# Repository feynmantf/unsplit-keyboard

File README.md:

# this project has been archived and abandoned in pursuit of hall-effect
# ~~WIP!! (firmware and schematic work but i havent gotten around to the new pcb layout) - I will get back to working on it when the semester ends/when I have the time~~
## all files in [early revisions/final but with microcontrollers](/early%20revisions/final%20but%20with%20microcontrollers) still work and can be manufactured (see [BOM](/early%20revisions/final%20but%20with%20microcontrollers/bom%20and%20cpl%20files) and [Gerber](/early%20revisions/final%20but%20with%20microcontrollers/gerber%20and%20drill%20files) folders), i just dont like the layout lol
## i plan on coming back to this project sometime before the end of 2024, but i cant promise it will look the same

# kaluza kb
kaluza kb pcb, layout, and case files (plus other useful stuff like firmware/images)
(documentation in progress)

## design logic
i wanted a keyboard that was both 65% and had extra function keys. i also wanted an oled panel and rotary encoder. and, as an added bonus, i love seeing through hole components on a keyboard. therefore, all of these features have been included

## sample images (they exist for the old revisions if you want to dig through the file tree)

### case images/renders:

### pcb images/renders:
#### pcb front (old version):

#### pcb back (old version):

### schematic (new version):

### handwired circuit test images:
.JPG)
.JPG)

## parts needed to build the board (not included in these files)
### parts you must source
- keyswitches (x80)
- keycaps (base kit and spacebar)
- pcb stabilizers (2u x4 and 6.25u x1)
- rotary knob (x1)
- rotary encoder (ec11 with switch) (x1)
- oled (0.91 inch, SSD1306) (x1)
- switch diodes (x80)
- elite-c v4 (x1)

### parts to get manufactured
- pcb
- plate (carbon fiber or sheet metal) (2mm)
- case (3d printed)
- leaf springs (carbon fiber) (1mm)

## basic instructions
- buy all the parts listed above
- get the pcb printed (from jlcpcb or some other service)
- get the plate, case, and leaf springs printed
- flash firmware and test the board to make sure everything works
- screw stabilizers into pcb
- align and place plate on top of pcb
- clip switches into place and slot them into the pcb
- solder switches to the pcb (locations marked on pcb)
- solder rotary encoder onto pcb (locations marked on pcb)
- solder oled panel onto pcb (locations marked on pcb)
- test everything again
- screw leaf springs into pcb (locations marked on pcb)
- put assembled pcb and plate in the case, and screw the case together
- you should be done now !!

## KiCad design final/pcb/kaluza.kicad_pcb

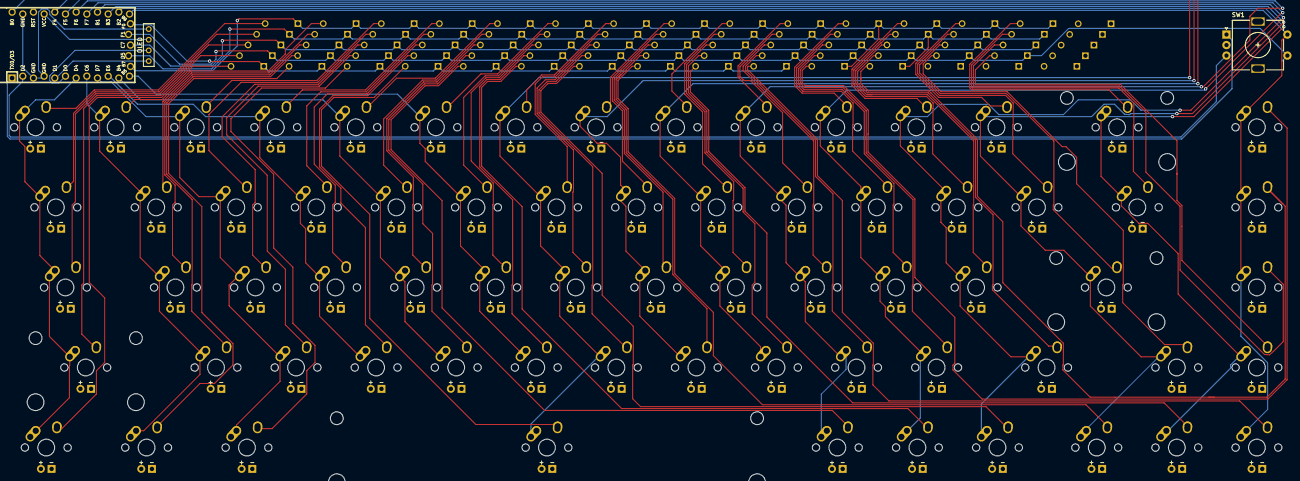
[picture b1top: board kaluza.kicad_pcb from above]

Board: 2 copper layers, 146 parts (0 on the bottom side), 94 nets.

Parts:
D1, D2, D3, D4, D5, D6, D7, D8, D9, D10, D11, D12, D13, D14, D15, D16, D17, D18, D19, D20, D21, D22, D23, D24, D25, D26, D27, D28, D29, D30, D31, D32, D33, D34, D35, D36, D37, D38, D39, D40, D41, D42, D43, D44, D45, D46, D47, D48, D49, D50, D51, D52, D53, D54, D55, D56, D57, D58, D59, D60, D61, D62, D63, D64, D65, D66, D67, D68: SMD_123; Diode-Hybrid-Back
D_Spare: SMD_123; Diode-Hybrid-Back
D_Spare#2, D_Spare#3, D_Spare#4, D_Spare#5, D_Spare#6, D_Spare#7: SMD_123; Diode-Hybrid-Back
MX1, MX2, MX3, MX4, MX5, MX6, MX7, MX8, MX9, MX10, MX11, MX12, MX13, MX15, MX17, MX18, MX19, MX20, MX21, MX22, MX23, MX24, MX25, MX26, MX27, MX28, MX30, MX32, MX33, MX34, MX35, MX36, MX37, MX38, MX39, MX40, MX41, MX42, MX44, MX46, MX47, MX48, MX49, MX50, MX51, MX52, MX53, MX54, MX55, MX57, MX58, MX63, MX64, MX65, MX66, MX67, MX68: MX-NoLED-MX_Alps_Hybrid; MX-1U
MX14: MX-NoLED-MX_Alps_Hybrid; MX-2U
MX16, MX29: MX-NoLED-MX_Alps_Hybrid; MX-1.5U
MX31, MX56: MX-NoLED-MX_Alps_Hybrid; MX-1.75U
MX43, MX45: MX-NoLED-MX_Alps_Hybrid; MX-2.25U
MX59, MX60, MX61: MX-NoLED-MX_Alps_Hybrid; MX-1.25U
MX62: MX-NoLED-MX_Alps_Hybrid; MX-6.25U
OL1: OLED-kbd; OLED
SW1: Rotary_Encoder_Switch; RotaryEncoder_Alps_EC11E-Switch_Vertical_H20mm
U1: Elite-C; Elite-C-ZigZag

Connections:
COL_0: MX1.1, MX16.1, MX31.1, MX45.1, MX59.1, U1.7
COL_1: MX2.1, MX17.1, MX32.1, MX46.1, MX60.1, U1.8
COL_2: MX3.1, MX18.1, MX33.1, MX47.1, MX61.1, U1.9
COL_3: MX4.1, MX19.1, MX34.1, MX48.1, U1.10
COL_4: MX5.1, MX20.1, MX35.1, MX49.1, U1.11
COL_5: MX6.1, MX21.1, MX36.1, MX50.1, U1.12
COL_6: MX7.1, MX22.1, MX37.1, MX51.1, MX62.1, U1.24
COL_7: MX8.1, MX23.1, MX38.1, MX52.1, U1.20
COL_8: MX9.1, MX24.1, MX39.1, MX53.1, U1.19
COL_9: MX10.1, MX25.1, MX40.1, MX54.1, MX63.1, U1.18
COL_10: MX11.1, MX26.1, MX41.1, MX55.1, MX64.1, U1.17
COL_11: MX12.1, MX27.1, MX42.1, MX56.1, MX65.1, U1.16
COL_12: MX13.1, MX28.1, MX43.1, MX57.1, MX66.1, U1.15
COL_13: MX14.1, MX29.1, MX58.1, MX67.1, U1.14
COL_14: MX15.1, MX30.1, MX44.1, MX68.1, SW1.S2, U1.13
GND: OL1.4, SW1.C, U1.3, U1.4, U1.23
unnamed: D1.2, MX1.2
unnamed: D2.2, MX2.2
unnamed: D3.2, MX3.2
unnamed: D4.2, MX4.2
unnamed: D5.2, MX5.2
unnamed: D6.2, MX6.2
unnamed: D7.2, MX7.2
unnamed: D8.2, MX8.2
unnamed: D9.2, MX9.2
unnamed: D10.2, MX10.2
unnamed: D11.2, MX11.2
unnamed: D12.2, MX12.2
unnamed: D13.2, MX13.2
unnamed: D14.2, MX14.2
unnamed: D15.2, MX15.2
unnamed: D16.2, MX16.2
unnamed: D17.2, MX17.2
unnamed: D18.2, MX18.2
unnamed: D19.2, MX19.2
unnamed: D20.2, MX20.2
unnamed: D21.2, MX21.2
unnamed: D22.2, MX22.2
unnamed: D23.2, MX23.2
unnamed: D24.2, MX24.2
unnamed: D25.2, MX25.2
unnamed: D26.2, MX26.2
unnamed: D27.2, MX27.2
unnamed: D28.2, MX28.2
unnamed: D29.2, MX29.2
unnamed: D30.2, MX30.2
unnamed: D31.2, MX31.2
unnamed: D32.2, MX32.2
unnamed: D33.2, MX33.2
unnamed: D34.2, MX34.2
unnamed: D35.2, MX35.2
unnamed: D36.2, MX36.2
unnamed: D37.2, MX37.2
unnamed: D38.2, MX38.2
unnamed: D39.2, MX39.2
unnamed: D40.2, MX40.2
unnamed: D41.2, MX41.2
unnamed: D42.2, MX42.2
unnamed: D43.2, MX43.2
unnamed: D44.2, MX44.2
unnamed: D45.2, MX45.2
unnamed: D46.2, MX46.2
unnamed: D47.2, MX47.2
unnamed: D48.2, MX48.2
unnamed: D49.2, MX49.2
unnamed: D50.2, MX50.2
unnamed: D51.2, MX51.2
unnamed: D52.2, MX52.2
unnamed: D53.2, MX53.2
unnamed: D54.2, MX54.2
unnamed: D55.2, MX55.2
unnamed: D56.2, MX56.2
unnamed: D57.2, MX57.2
unnamed: D58.2, MX58.2
unnamed: D59.2, MX59.2
unnamed: D60.2, MX60.2
unnamed: D61.2, MX61.2
unnamed: D62.2, MX62.2
unnamed: D63.2, MX63.2
unnamed: D64.2, MX64.2
unnamed: D65.2, MX65.2
unnamed: D66.2, MX66.2
unnamed: D67.2, MX67.2
unnamed: D68.2, MX68.2
ROT_A: SW1.A, U1.1
ROT_B: SW1.B, U1.2
ROW0: D1.1, D2.1, D3.1, D4.1, D5.1, D6.1, D7.1, D8.1, D9.1, D10.1, D11.1, D12.1, D13.1, D14.1, D15.1, U1.25
ROW1: D16.1, D17.1, D18.1, D19.1, D20.1, D21.1, D22.1, D23.1, D24.1, D25.1, D26.1, D27.1, D28.1, D29.1, D30.1, U1.26
ROW2: D31.1, D32.1, D33.1, D34.1, D35.1, D36.1, D37.1, D38.1, D39.1, D40.1, D41.1, D42.1, D43.1, D44.1, U1.27
ROW3: D45.1, D46.1, D47.1, D48.1, D49.1, D50.1, D51.1, D52.1, D53.1, D54.1, D55.1, D56.1, D57.1, D58.1, SW1.S1, U1.28
ROW4: D59.1, D60.1, D61.1, D62.1, D63.1, D64.1, D65.1, D66.1, D67.1, D68.1, U1.29
SCL: OL1.2, U1.6
SDA: OL1.1, U1.5
VCC: OL1.3, U1.21

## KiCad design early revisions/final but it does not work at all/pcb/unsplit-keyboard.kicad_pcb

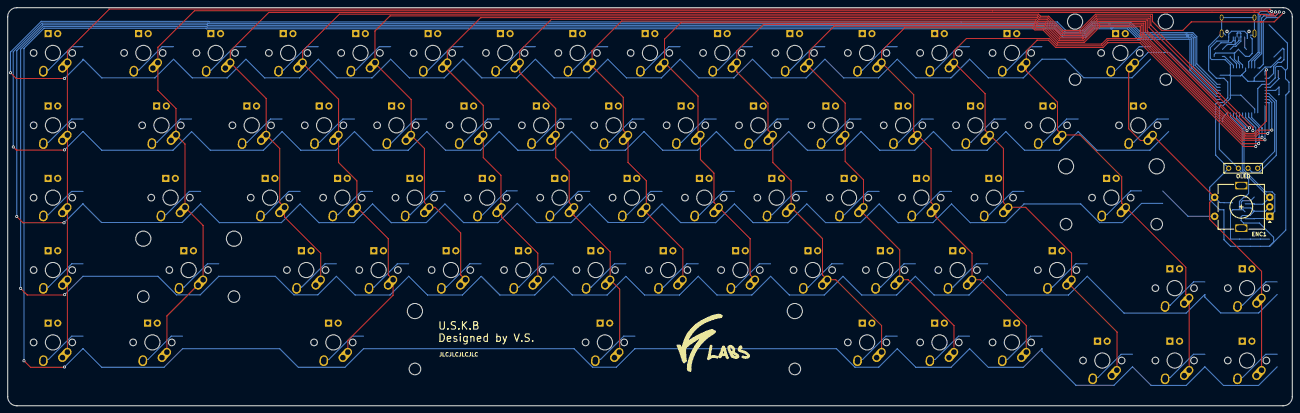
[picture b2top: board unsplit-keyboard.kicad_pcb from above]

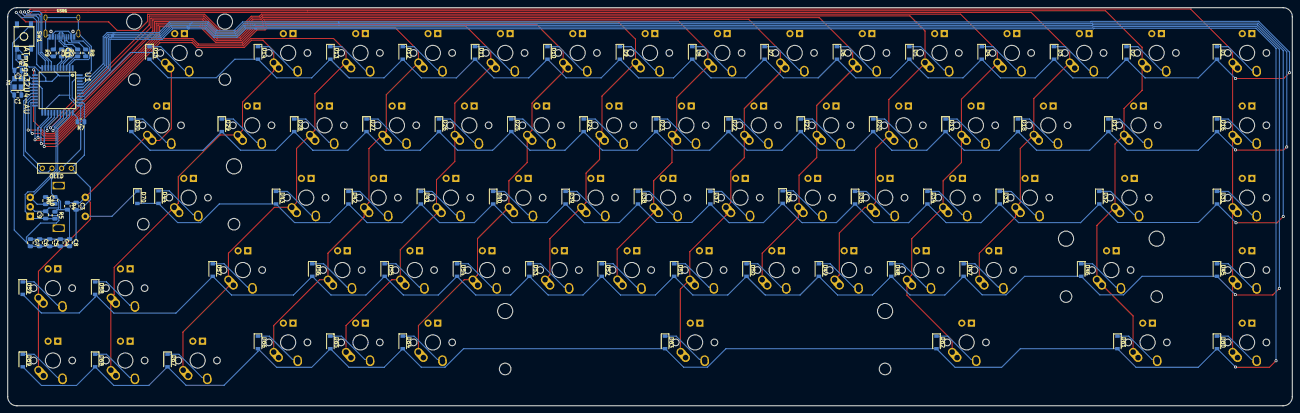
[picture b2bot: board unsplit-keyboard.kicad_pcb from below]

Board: 2 copper layers, 338.1 x 104.8 mm, 167 parts (94 on the bottom side), 107 nets.

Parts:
C1, C2: 22p; C_0805_2012Metric
C3, C4, C5, C6, C7, C9, C10: 0.1u; C_0805_2012Metric
C8: 4.7u; C_0805_2012Metric
C11: 1u; C_0805_2012Metric
D1, D2, D3, D4, D5, D6, D7, D8, D9, D10, D11, D12, D13, D14, D15, D16, D17, D18, D19, D20, D21, D22, D23, D24, D25, D26, D27, D28, D29, D30, D31, D32, D33, D34, D35, D36, D37, D38, D39, D40, D41, D42, D43, D44, D45, D46, D47, D48, D49, D50, D51, D52, D53, D54, D55, D56, D57, D58, D59, D60, D61, D62, D63, D64, D65, D66, D67, D68, D69, D70: D; D_SOD-123
ENC1: Rotary_Encoder_Switch; RotaryEncoder_Alps_EC11E-Switch_Vertical_H20mm
LOGO1: LOGO; logo
LOGO2: LOGO; labs
MX1, MX2, MX3, MX4, MX5, MX6, MX7, MX8, MX9, MX10, MX11, MX12, MX13, MX14, MX16, MX18, MX19, MX20, MX21, MX22, MX23, MX24, MX25, MX26, MX27, MX28, MX29, MX31, MX33, MX34, MX35, MX36, MX37, MX38, MX39, MX40, MX41, MX42, MX43, MX45, MX47, MX48, MX49, MX50, MX51, MX52, MX53, MX54, MX55, MX56, MX58, MX59, MX60, MX64, MX65, MX66, MX67, MX68, MX69: MX-NoLED-MX_Alps_Hybrid; MX-1U
MX15: MX-NoLED-MX_Alps_Hybrid; MX-2U
MX17, MX30: MX-NoLED-MX_Alps_Hybrid; MX-1.5U
MX32, MX57: MX-NoLED-MX_Alps_Hybrid; MX-1.75U
MX44, MX46: MX-NoLED-MX_Alps_Hybrid; MX-2.25U
MX61, MX62: MX-NoLED-MX_Alps_Hybrid; MX-1.25U
MX63: MX-NoLED-MX_Alps_Hybrid; MX-6.25U
OL1: OLED-kbd; OLED
R1, R4, R5, R6, R7: 10k; R_0805_2012Metric
R2, R3: 22; R_0805_2012Metric
R8, R9: 5.1k; R_0805_2012Metric
SW1: SW_PUSH; SKQG-1155865
U1: ATmega32U4-AU; ATMEGA32U4-AU
USB1: HRO-TYPE-C-31-M-12; HRO-TYPE-C-31-M-12-Assembly
X1: XTAL_GND; Crystal_SMD_3225-4pin_3.2x2.5mm

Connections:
COL0: MX1.1, MX16.1, MX31.1, MX45.1, MX60.1, U1.8
COL1: MX2.1, MX17.1, MX32.1, MX46.1, MX61.1, U1.9
COL2: MX3.1, MX18.1, MX33.1, MX47.1, U1.10
COL3: MX4.1, MX19.1, MX34.1, MX48.1, MX62.1, U1.11
COL4: MX5.1, MX20.1, MX35.1, MX49.1, U1.28
COL5: MX6.1, MX21.1, MX36.1, MX50.1, U1.29
COL6: MX7.1, MX22.1, MX37.1, MX51.1, MX63.1, U1.30
COL7: MX8.1, MX23.1, MX38.1, MX52.1, U1.12
COL8: MX9.1, MX24.1, MX39.1, MX53.1, U1.20
COL9: MX10.1, MX25.1, MX40.1, MX54.1, MX64.1, U1.21
COL10: MX11.1, MX26.1, MX41.1, MX55.1, MX65.1, U1.25
COL11: MX12.1, MX27.1, MX42.1, MX56.1, MX66.1, U1.22
COL12: MX13.1, MX28.1, MX43.1, MX57.1, MX67.1, U1.26
COL13: MX14.1, MX29.1, MX44.1, MX58.1, MX68.1, U1.27
COL14: C3.1, ENC1.S1, MX15.1, MX30.1, MX59.1, MX69.1, R4.1, U1.36
D+: R3.1, U1.4
D-: R2.1, U1.3
GND: C1.2, C2.2, C3.2, C4.2, C5.2, C6.2, C7.2, C8.2, C9.2, C10.1, C11.1, ENC1.C, OL1.4, R7.1, R8.2, R9.1, SW1.1, U1.5, U1.15, U1.23, U1.35, U1.43, USB1.1, USB1.12, USB1.13, X1.3
unnamed: C11.2, U1.6
unnamed: D1.1, MX1.2
unnamed: D2.1, MX2.2
unnamed: D3.1, MX3.2
unnamed: D4.1, MX4.2
unnamed: D5.1, MX5.2
unnamed: D6.1, MX6.2
unnamed: D7.1, MX7.2
unnamed: D8.1, MX8.2
unnamed: D9.1, MX9.2
unnamed: D10.1, MX10.2
unnamed: D11.1, MX11.2
unnamed: D12.1, MX12.2
unnamed: D13.1, MX13.2
unnamed: D14.1, MX14.2
unnamed: D15.1, MX15.2
unnamed: D16.1, MX16.2
unnamed: D17.1, MX17.2
unnamed: D18.1, MX18.2
unnamed: D19.1, MX19.2
unnamed: D20.1, MX20.2
unnamed: D21.1, MX21.2
unnamed: D22.1, MX22.2
unnamed: D23.1, MX23.2
unnamed: D24.1, MX24.2
unnamed: D25.1, MX25.2
unnamed: D26.1, MX26.2
unnamed: D27.1, MX27.2
unnamed: D28.1, MX28.2
unnamed: D29.1, MX29.2
unnamed: D30.1, MX30.2
unnamed: D31.1, MX31.2
unnamed: D32.1, MX32.2
unnamed: D33.1, MX33.2
unnamed: D34.1, MX34.2
unnamed: D35.1, MX35.2
unnamed: D36.1, MX36.2
unnamed: D37.1, MX37.2
unnamed: D38.1, MX38.2
unnamed: D39.1, MX39.2
unnamed: D40.1, MX40.2
unnamed: D41.1, MX41.2
unnamed: D42.1, MX42.2
unnamed: D43.1, MX43.2
unnamed: D44.1, MX44.2
unnamed: D45.1, MX45.2
unnamed: D46.1, MX46.2
unnamed: D47.1, MX47.2
unnamed: D48.1, MX48.2
unnamed: D49.1, MX49.2
unnamed: D50.1, MX50.2
unnamed: D51.1, MX51.2
unnamed: D52.1, MX52.2
unnamed: D53.1, MX53.2
unnamed: D54.1, MX54.2
unnamed: D55.1, MX55.2
unnamed: D56.1, MX56.2
unnamed: D57.1, MX57.2
unnamed: D58.1, MX58.2
unnamed: D59.1, MX59.2
unnamed: D60.1, MX60.2
unnamed: D61.1, MX61.2
unnamed: D62.1, MX62.2
unnamed: D63.1, MX63.2
unnamed: D64.1, MX64.2
unnamed: D65.1, MX65.2
unnamed: D66.1, MX66.2
unnamed: D67.1, MX67.2
unnamed: D68.1, MX68.2
unnamed: D69.1, MX69.2
unnamed: R2.2, USB1.5, USB1.7
unnamed: R3.2, USB1.6, USB1.8
unnamed: R7.2, U1.33
unnamed: R8.1, USB1.4
unnamed: R9.2, USB1.10
RESET: R1.1, SW1.2, U1.13
ROT_A: C9.1, ENC1.A, R5.2, U1.31
ROT_B: C10.2, ENC1.B, R6.1, U1.32
ROW0: D1.2, D2.2, D3.2, D4.2, D5.2, D6.2, D7.2, D8.2, D9.2, D10.2, D11.2, D12.2, D13.2, D14.2, D15.2, U1.41
ROW1: D16.2, D17.2, D18.2, D19.2, D20.2, D21.2, D22.2, D23.2, D24.2, D25.2, D26.2, D27.2, D28.2, D29.2, D30.2, U1.40
ROW2: D31.2, D32.2, D33.2, D34.2, D35.2, D36.2, D37.2, D38.2, D39.2, D40.2, D41.2, D42.2, D43.2, D44.2, D70.2, U1.39
ROW3: D45.2, D46.2, D47.2, D48.2, D49.2, D50.2, D51.2, D52.2, D53.2, D54.2, D55.2, D56.2, D57.2, D58.2, D59.2, U1.38
ROW4: D60.2, D61.2, D62.2, D63.2, D64.2, D65.2, D66.2, D67.2, D68.2, D69.2, U1.37
R_ENC: D70.1, ENC1.S2
SCL: OL1.2, U1.18
SDA: OL1.1, U1.19
VCC: C4.1, C5.1, C6.1, C7.1, C8.1, OL1.3, R1.2, R4.2, R5.1, R6.2, U1.2, U1.7, U1.14, U1.24, U1.34, U1.44, USB1.2, USB1.11
XTAL1: C1.1, U1.17, X1.1
XTAL2: C2.1, U1.16, X1.2

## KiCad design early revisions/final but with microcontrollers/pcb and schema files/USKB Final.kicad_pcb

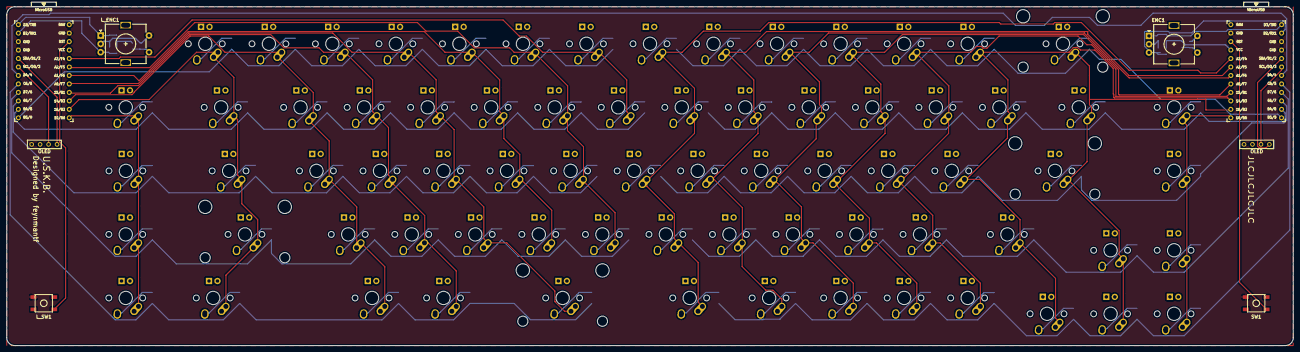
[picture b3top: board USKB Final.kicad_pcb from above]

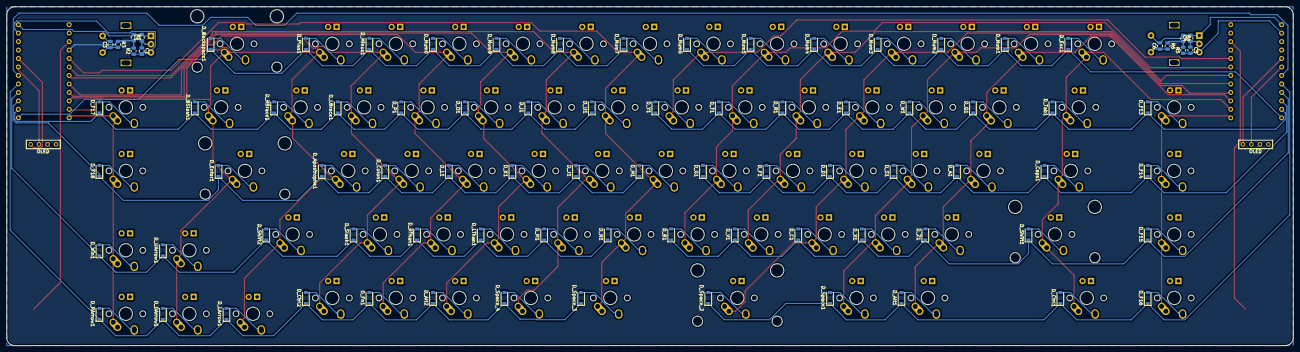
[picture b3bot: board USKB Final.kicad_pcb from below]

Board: 2 copper layers, 385.8 x 101.6 mm, 166 parts (85 on the bottom side), 114 nets.

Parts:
C1, C2, C3, C4, C5, C6: 0.1u; C_0805_2012Metric
D_A1: SMD_123; D_SOD-123
D_Alt1, D_Alt2: SMD_123; D_SOD-123
D_Apostrophe1: SMD_123; D_SOD-123
D_B1: SMD_123; D_SOD-123
D_BSlash1: SMD_123; D_SOD-123
D_Backspace1: SMD_123; D_SOD-123
D_C1: SMD_123; D_SOD-123
D_Caps1: SMD_123; D_SOD-123
D_Colon1: SMD_123; D_SOD-123
D_Ctrl1, D_Ctrl2: SMD_123; D_SOD-123
D_D1: SMD_123; D_SOD-123
D_DArrow1: SMD_123; D_SOD-123
D_E1: SMD_123; D_SOD-123
D_Enter1: SMD_123; D_SOD-123
D_Esc1: SMD_123; D_SOD-123
D_F1, D_F13, D_F14, D_F15, D_F16, D_F17, D_F18: SMD_123; D_SOD-123
D_Fn1: SMD_123; D_SOD-123
D_G1: SMD_123; D_SOD-123
D_H1: SMD_123; D_SOD-123
D_I1: SMD_123; D_SOD-123
D_J1: SMD_123; D_SOD-123
D_K1: SMD_123; D_SOD-123
D_L1: SMD_123; D_SOD-123
D_LArrow1: SMD_123; D_SOD-123
D_LBrace1: SMD_123; D_SOD-123
D_LThan1: SMD_123; D_SOD-123
D_M1: SMD_123; D_SOD-123
D_Minus1: SMD_123; D_SOD-123
D_N1: SMD_123; D_SOD-123
D_Num0, D_Num1, D_Num2, D_Num3, D_Num4, D_Num5, D_Num6, D_Num7, D_Num8, D_Num9: SMD_123; D_SOD-123
D_O1: SMD_123; D_SOD-123
D_P1: SMD_123; D_SOD-123
D_Plus1: SMD_123; D_SOD-123
D_Q1: SMD_123; D_SOD-123
D_R1: SMD_123; D_SOD-123
D_RArrow1: SMD_123; D_SOD-123
D_RBrace1: SMD_123; D_SOD-123
D_RThan1: SMD_123; D_SOD-123
D_S1: SMD_123; D_SOD-123
D_Shift1, D_Shift2: SMD_123; D_SOD-123
D_Slash1: SMD_123; D_SOD-123
D_Space1: SMD_123; D_SOD-123
D_Space_2, D_Space_3, D_Space_4: SMD_123; D_SOD-123
D_T1: SMD_123; D_SOD-123
D_Tab1: SMD_123; D_SOD-123
D_U1: SMD_123; D_SOD-123
D_UArrow1: SMD_123; D_SOD-123
D_V1: SMD_123; D_SOD-123
D_W1: SMD_123; D_SOD-123
D_Win1: SMD_123; D_SOD-123
D_X1: SMD_123; D_SOD-123
D_Y1: SMD_123; D_SOD-123
D_Z1: SMD_123; D_SOD-123
ENC1: Rotary_Encoder_Switch; RotaryEncoder_Alps_EC11E-Switch_Vertical_H20mm
K_A1: MX-NoLED; MX-1U
K_Alt1: MX-NoLED; MX-1.25U
K_Alt2: MX-NoLED; MX-1U
K_Apostrophe1: MX-NoLED; MX-1U
K_B1: MX-NoLED; MX-1U
K_BSlash1: MX-NoLED; MX-1.5U
K_Backspace1: MX-NoLED; MX-2U
K_C1: MX-NoLED; MX-1U
K_Caps1: MX-NoLED; MX-1.75U
K_Colon1: MX-NoLED; MX-1U
K_Ctrl1: MX-NoLED; MX-1.25U
K_Ctrl2: MX-NoLED; MX-1U
K_D1: MX-NoLED; MX-1U
K_DArrow1: MX-NoLED; MX-1U
K_E1: MX-NoLED; MX-1U
K_Enter1: MX-NoLED; MX-2.25U
K_Esc1: MX-NoLED; MX-1U
K_F1, K_F13, K_F14, K_F15, K_F16, K_F17, K_F18: MX-NoLED; MX-1U
K_Fn1: MX-NoLED; MX-1U
K_G1: MX-NoLED; MX-1U
K_H1: MX-NoLED; MX-1U
K_I1: MX-NoLED; MX-1U
K_J1: MX-NoLED; MX-1U
K_K1: MX-NoLED; MX-1U
K_L1: MX-NoLED; MX-1U
K_LArrow1: MX-NoLED; MX-1U
K_LBrace1: MX-NoLED; MX-1U
K_LThan1: MX-NoLED; MX-1U
K_M1: MX-NoLED; MX-1U
K_Minus1: MX-NoLED; MX-1U
K_N1: MX-NoLED; MX-1U
K_Num0, K_Num1, K_Num2, K_Num3, K_Num4, K_Num5, K_Num6, K_Num7, K_Num8, K_Num9: MX-NoLED; MX-1U
K_O1: MX-NoLED; MX-1U
K_P1: MX-NoLED; MX-1U
K_Plus1: MX-NoLED; MX-1U
K_Q1: MX-NoLED; MX-1U
K_R1: MX-NoLED; MX-1U
K_RArrow1: MX-NoLED; MX-1U
K_RBrace1: MX-NoLED; MX-1U
K_RThan1: MX-NoLED; MX-1U
K_S1: MX-NoLED; MX-1U
K_Shift1: MX-NoLED; MX-2.25U
K_Shift2: MX-NoLED; MX-1.75U
K_Slash1: MX-NoLED; MX-1U
K_Space1: MX-NoLED; MX-1U
K_Space_2: MX-NoLED; MX-2.75U
K_Space_3, K_Space_4: MX-NoLED; MX-1.25U
K_T1: MX-NoLED; MX-1U
K_Tab1: MX-NoLED; MX-1.5U
K_U1: MX-NoLED; MX-1U
K_UArrow1: MX-NoLED; MX-1U
K_V1: MX-NoLED; MX-1U
K_W1: MX-NoLED; MX-1U
K_Win1: MX-NoLED; MX-1U
K_X1: MX-NoLED; MX-1U
K_Y1: MX-NoLED; MX-1U
K_Z1: MX-NoLED; MX-1U
L_ENC1: Rotary_Encoder_Switch; RotaryEncoder_Alps_EC11E-Switch_Vertical_H20mm
L_OL1: OLED
L_SW1: SW_PUSH; SKQG-1155865
L_U1: ProMicro; ProMicro_v3
OL1: OLED
R1, R2, R3, R4, R5, R6: 10k; R_0805_2012Metric
SW1: SW_PUSH; SKQG-1155865
U1: ProMicro; ProMicro_v3

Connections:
COL0: K_H1.1, K_N1.1, K_Num7.1, K_Space_3.1, K_U1.1, U1.20
COL1: K_I1.1, K_J1.1, K_M1.1, K_Num8.1, K_Space_4.1, U1.19
COL2: K_Alt2.1, K_K1.1, K_LThan1.1, K_Num9.1, K_O1.1, U1.18
COL3: K_Fn1.1, K_L1.1, K_Num0.1, K_P1.1, K_RThan1.1, U1.17
COL4: K_Colon1.1, K_Ctrl2.1, K_LBrace1.1, K_Minus1.1, K_Slash1.1, U1.16
COL5: K_Apostrophe1.1, K_LArrow1.1, K_Plus1.1, K_RBrace1.1, K_Shift2.1, U1.15
COL6: K_BSlash1.1, K_Backspace1.1, K_DArrow1.1, K_Enter1.1, K_UArrow1.1, U1.14
COL7: K_F17.1, K_F18.1, K_RArrow1.1, K_Win1.1, U1.13
DATA: L_U1.7, U1.7
GND: C1.1, C2.1, C3.2, C4.1, C5.1, C6.2, ENC1.C, ENC1.S2, L_ENC1.C, L_ENC1.S2, L_OL1.4, L_SW1.2, L_U1.3, L_U1.4, L_U1.23, OL1.4, SW1.2, U1.3, U1.4, U1.23
K_ENC: C3.1, ENC1.S1, R3.2
L_COL0: K_F13.1, K_F14.1, K_F15.1, K_F16.1, L_U1.13
L_COL1: K_Caps1.1, K_Ctrl1.1, K_Esc1.1, K_Shift1.1, K_Tab1.1, L_U1.14
L_COL2: K_A1.1, K_Alt1.1, K_Num1.1, K_Q1.1, K_Z1.1, L_U1.15
L_COL3: K_Num2.1, K_S1.1, K_Space1.1, K_W1.1, K_X1.1, L_U1.16
L_COL4: K_C1.1, K_D1.1, K_E1.1, K_Num3.1, K_Space_2.1, L_U1.17
L_COL5: K_F1.1, K_Num4.1, K_R1.1, K_V1.1, L_U1.18
L_COL6: K_B1.1, K_G1.1, K_Num5.1, K_T1.1, L_U1.19
L_COL7: K_Num6.1, K_Y1.1, L_U1.20
L_K_ENC: C6.1, L_ENC1.S1, R6.2
L_RESET: L_SW1.1, L_U1.22
L_ROT_A: C4.2, L_ENC1.A, L_U1.1, R4.1
L_ROT_B: C5.2, L_ENC1.B, L_U1.2, R5.1
L_ROW0: D_Esc1.1, D_Num1.1, D_Num2.1, D_Num3.1, D_Num4.1, D_Num5.1, D_Num6.1, L_U1.12
L_ROW1: D_E1.1, D_F13.1, D_Q1.1, D_R1.1, D_T1.1, D_Tab1.1, D_W1.1, D_Y1.1, L_U1.11
L_ROW2: D_A1.1, D_Caps1.1, D_D1.1, D_F1.1, D_F14.1, D_G1.1, D_S1.1, L_U1.10
L_ROW3: D_B1.1, D_C1.1, D_F15.1, D_Shift1.1, D_V1.1, D_X1.1, D_Z1.1, L_U1.9
L_ROW4: D_Alt1.1, D_Ctrl1.1, D_F16.1, D_Space1.1, D_Space_2.1, L_U1.8
L_SCL: L_OL1.2, L_U1.6
L_SDA: L_OL1.1, L_U1.5
unnamed: D_A1.2, K_A1.2
unnamed: D_Alt1.2, K_Alt1.2
unnamed: D_Alt2.2, K_Alt2.2
unnamed: D_Apostrophe1.2, K_Apostrophe1.2
unnamed: D_B1.2, K_B1.2
unnamed: D_BSlash1.2, K_BSlash1.2
unnamed: D_Backspace1.2, K_Backspace1.2
unnamed: D_C1.2, K_C1.2
unnamed: D_Caps1.2, K_Caps1.2
unnamed: D_Colon1.2, K_Colon1.2
unnamed: D_Ctrl1.2, K_Ctrl1.2
unnamed: D_Ctrl2.2, K_Ctrl2.2
unnamed: D_D1.2, K_D1.2
unnamed: D_DArrow1.2, K_DArrow1.2
unnamed: D_E1.2, K_E1.2
unnamed: D_Enter1.2, K_Enter1.2
unnamed: D_Esc1.2, K_Esc1.2
unnamed: D_F1.2, K_F1.2
unnamed: D_F13.2, K_F13.2
unnamed: D_F14.2, K_F14.2
unnamed: D_F15.2, K_F15.2
unnamed: D_F16.2, K_F16.2
unnamed: D_F17.2, K_F17.2
unnamed: D_F18.2, K_F18.2
unnamed: D_Fn1.2, K_Fn1.2
unnamed: D_G1.2, K_G1.2
unnamed: D_H1.2, K_H1.2
unnamed: D_I1.2, K_I1.2
unnamed: D_J1.2, K_J1.2
unnamed: D_K1.2, K_K1.2
unnamed: D_L1.2, K_L1.2
unnamed: D_LArrow1.2, K_LArrow1.2
unnamed: D_LBrace1.2, K_LBrace1.2
unnamed: D_LThan1.2, K_LThan1.2
unnamed: D_M1.2, K_M1.2
unnamed: D_Minus1.2, K_Minus1.2
unnamed: D_N1.2, K_N1.2
unnamed: D_Num0.2, K_Num0.2
unnamed: D_Num1.2, K_Num1.2
unnamed: D_Num2.2, K_Num2.2
unnamed: D_Num3.2, K_Num3.2
unnamed: D_Num4.2, K_Num4.2
unnamed: D_Num5.2, K_Num5.2
unnamed: D_Num6.2, K_Num6.2
unnamed: D_Num7.2, K_Num7.2
unnamed: D_Num8.2, K_Num8.2
unnamed: D_Num9.2, K_Num9.2
unnamed: D_O1.2, K_O1.2
unnamed: D_P1.2, K_P1.2
unnamed: D_Plus1.2, K_Plus1.2
unnamed: D_Q1.2, K_Q1.2
unnamed: D_R1.2, K_R1.2
unnamed: D_RArrow1.2, K_RArrow1.2
unnamed: D_RBrace1.2, K_RBrace1.2
unnamed: D_RThan1.2, K_RThan1.2
unnamed: D_S1.2, K_S1.2
unnamed: D_Shift1.2, K_Shift1.2
unnamed: D_Shift2.2, K_Shift2.2
unnamed: D_Slash1.2, K_Slash1.2
unnamed: D_Space1.2, K_Space1.2
unnamed: D_Space_2.2, K_Space_2.2
unnamed: D_Space_3.2, K_Space_3.2
unnamed: D_Space_4.2, K_Space_4.2
unnamed: D_T1.2, K_T1.2
unnamed: D_Tab1.2, K_Tab1.2
unnamed: D_U1.2, K_U1.2
unnamed: D_UArrow1.2, K_UArrow1.2
unnamed: D_V1.2, K_V1.2
unnamed: D_W1.2, K_W1.2
unnamed: D_Win1.2, K_Win1.2
unnamed: D_X1.2, K_X1.2
unnamed: D_Y1.2, K_Y1.2
unnamed: D_Z1.2, K_Z1.2
RESET: SW1.1, U1.22
ROT_A: C1.2, ENC1.A, R1.1, U1.1
ROT_B: C2.2, ENC1.B, R2.1, U1.2
ROW0: D_Backspace1.1, D_Minus1.1, D_Num0.1, D_Num7.1, D_Num8.1, D_Num9.1, D_Plus1.1, U1.12
ROW1: D_BSlash1.1, D_F17.1, D_I1.1, D_LBrace1.1, D_O1.1, D_P1.1, D_RBrace1.1, D_U1.1, U1.11
ROW2: D_Apostrophe1.1, D_Colon1.1, D_Enter1.1, D_F18.1, D_H1.1, D_J1.1, D_K1.1, D_L1.1, U1.10
ROW3: D_LThan1.1, D_M1.1, D_N1.1, D_RThan1.1, D_Shift2.1, D_Slash1.1, D_UArrow1.1, D_Win1.1, U1.9
ROW4: D_Alt2.1, D_Ctrl2.1, D_DArrow1.1, D_Fn1.1, D_LArrow1.1, D_RArrow1.1, D_Space_3.1, D_Space_4.1, U1.8
SCL: OL1.2, U1.6
SDA: OL1.1, U1.5
VCC: L_OL1.3, L_U1.21, OL1.3, R1.2, R2.2, R3.1, R4.2, R5.2, R6.1, U1.21

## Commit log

2021-03-08 initialize project
2021-03-08 added submodules
2021-03-08 added libraries
2021-03-09 basic schematic (no footprints yet)
2021-03-09 added footprints
2021-03-09 saved lol
2021-03-09 finished pcb
2021-03-09 moved test board to new folder
2021-03-09 started new board / added libraries
2021-03-10 added libs for new schema
2021-03-10 started a little on pro micro version
2021-03-10 small updates
2021-03-11 left side done plus cleanup of folders and stuff
2021-03-11 finished sechma
2021-03-11 trying to fix library errors in kicad
2021-03-11 new library and assigned footprints to schematic
2021-03-11 laid out keys on pcb still need to do diodes and stuff
2021-03-12 finished first routing
2021-03-12 moved libraries and created rev 2 file
2021-03-12 autosave ig
2021-03-12 finalized traces
2021-03-12 finalized pcb design
2021-03-12 changed names on 2 files
2021-03-12 Create LICENSE
2021-03-12 Revert "Delete LICENSE"
    This reverts commit b7e25346c01ba6577a13f5b5bb47305c928c9c94.
2021-03-12 organized and exported files
2021-03-12 made gerbers
2021-03-12 generated bom and cpl
2021-03-13 changed files lol
2021-03-14 updated footprints and cpl to match cap set
2021-03-15 made cad for plate, made gerbers and a bunch of other stuff
2021-04-13 i realized a fatal error
2021-04-13 made necessary changes i think (kinda tempted to rewire the whole thing but drc runs perfectly soooooo)
2021-04-13 made plate files and maybe rest of case files too but thatll be expensive soooo
2021-04-14 adjusted plate/case files to be aligned with pcb hopefully
2021-04-14 i closed autocad and it deleted the automated backups
2021-04-15 did a bunch of stuff, but the main thing is make all of the case files almost perfect
2021-04-15 finalized plate and case files fixed space bars and created a hole for reset switch
2021-04-15 added pcb svgs
2021-04-15 removed title block from svgs
2021-04-16 moved some stuff around lmao
2021-04-16 testing smt with images
2021-04-16 okay test worked lol
2021-05-04 changed bottom row to be more accessible
2021-05-04 fixed reset switch cutout size
2021-05-06 fixed duplicate and overlapping cuts
2021-05-06 changed smt lol
2021-06-05 fixed stuff idk what tho
2021-07-08 new pcb beginnings
2021-07-10 fixed almost everything on the entire keyboard
    only need to buy new oled panel and test it, then layout new pcb, print them, layout new plate file, print it, and make a new case
2021-07-10 updated readme to make more sense with changes made to rest of board
2021-07-10 moved stuff and updated parts list
2021-07-10 change resistor amounts
2021-07-10 firmware files uploaded
2021-07-10 fixed layout
2021-07-14 everything but simulation done
2021-07-14 fixed 3d part library and bom
2021-07-14 added images
2021-07-16 updated gerbers and all that
2021-07-18 finalized rev 2 and ordered on jlc
2021-07-19 fixed footprint for diodes and finalized plate file
2021-08-12 idk what changed
2021-08-29 renaming to kaluza p1
2021-11-14 new layout
2021-11-14 laid out basically everything but diodes on pcb
2021-11-28 added firmware files
2022-06-02 apparently qmk did an update
2022-09-21 small update + looking at chip info
2022-09-28 test commit
2022-09-29 created schema image for final and added photos of the handwired board
2023-10-22 sync local backups
2023-10-22 updated readme with future plans
